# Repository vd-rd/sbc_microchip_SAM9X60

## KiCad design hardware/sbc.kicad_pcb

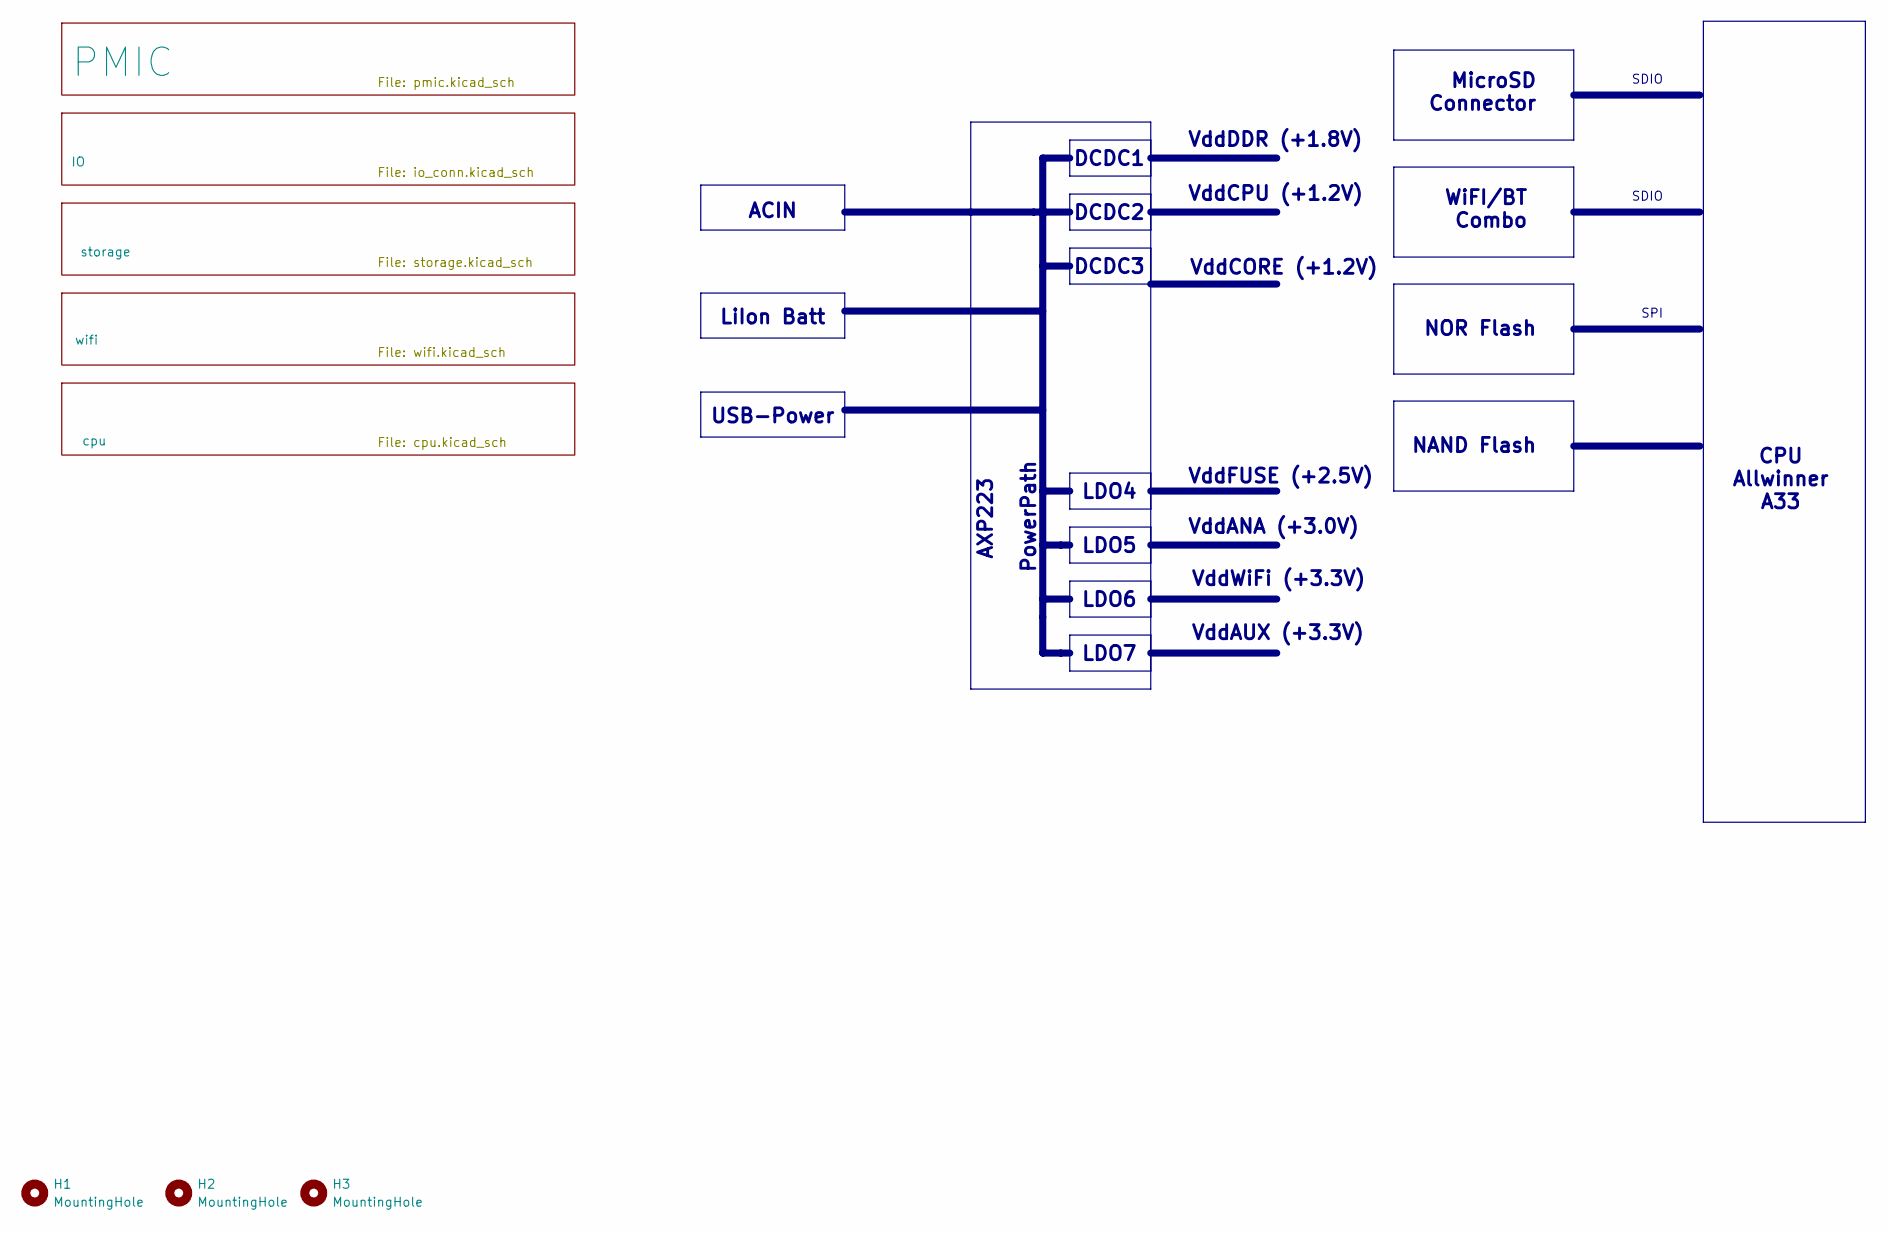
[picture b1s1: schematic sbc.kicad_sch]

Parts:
H1, H2, H3: MountingHole; MountingHole_2.7mm_M2.5

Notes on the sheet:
VddANA (+3.0V)
NOR Flash
LiIon Batt
WiFI/BT Combo
LDO7
LDO6
VddCORE (+1.2V)
DCDC1
PowerPath
SPI
VddWiFi (+3.3V)
DCDC2
CPU Allwinner A33
VddCPU (+1.2V)
SDIO
VddFUSE (+2.5V)
DCDC3
USB-Power
MicroSD Connector
LDO5
VddAUX (+3.3V)
VddDDR (+1.8V)
AXP223
ACIN
NAND Flash
LDO4

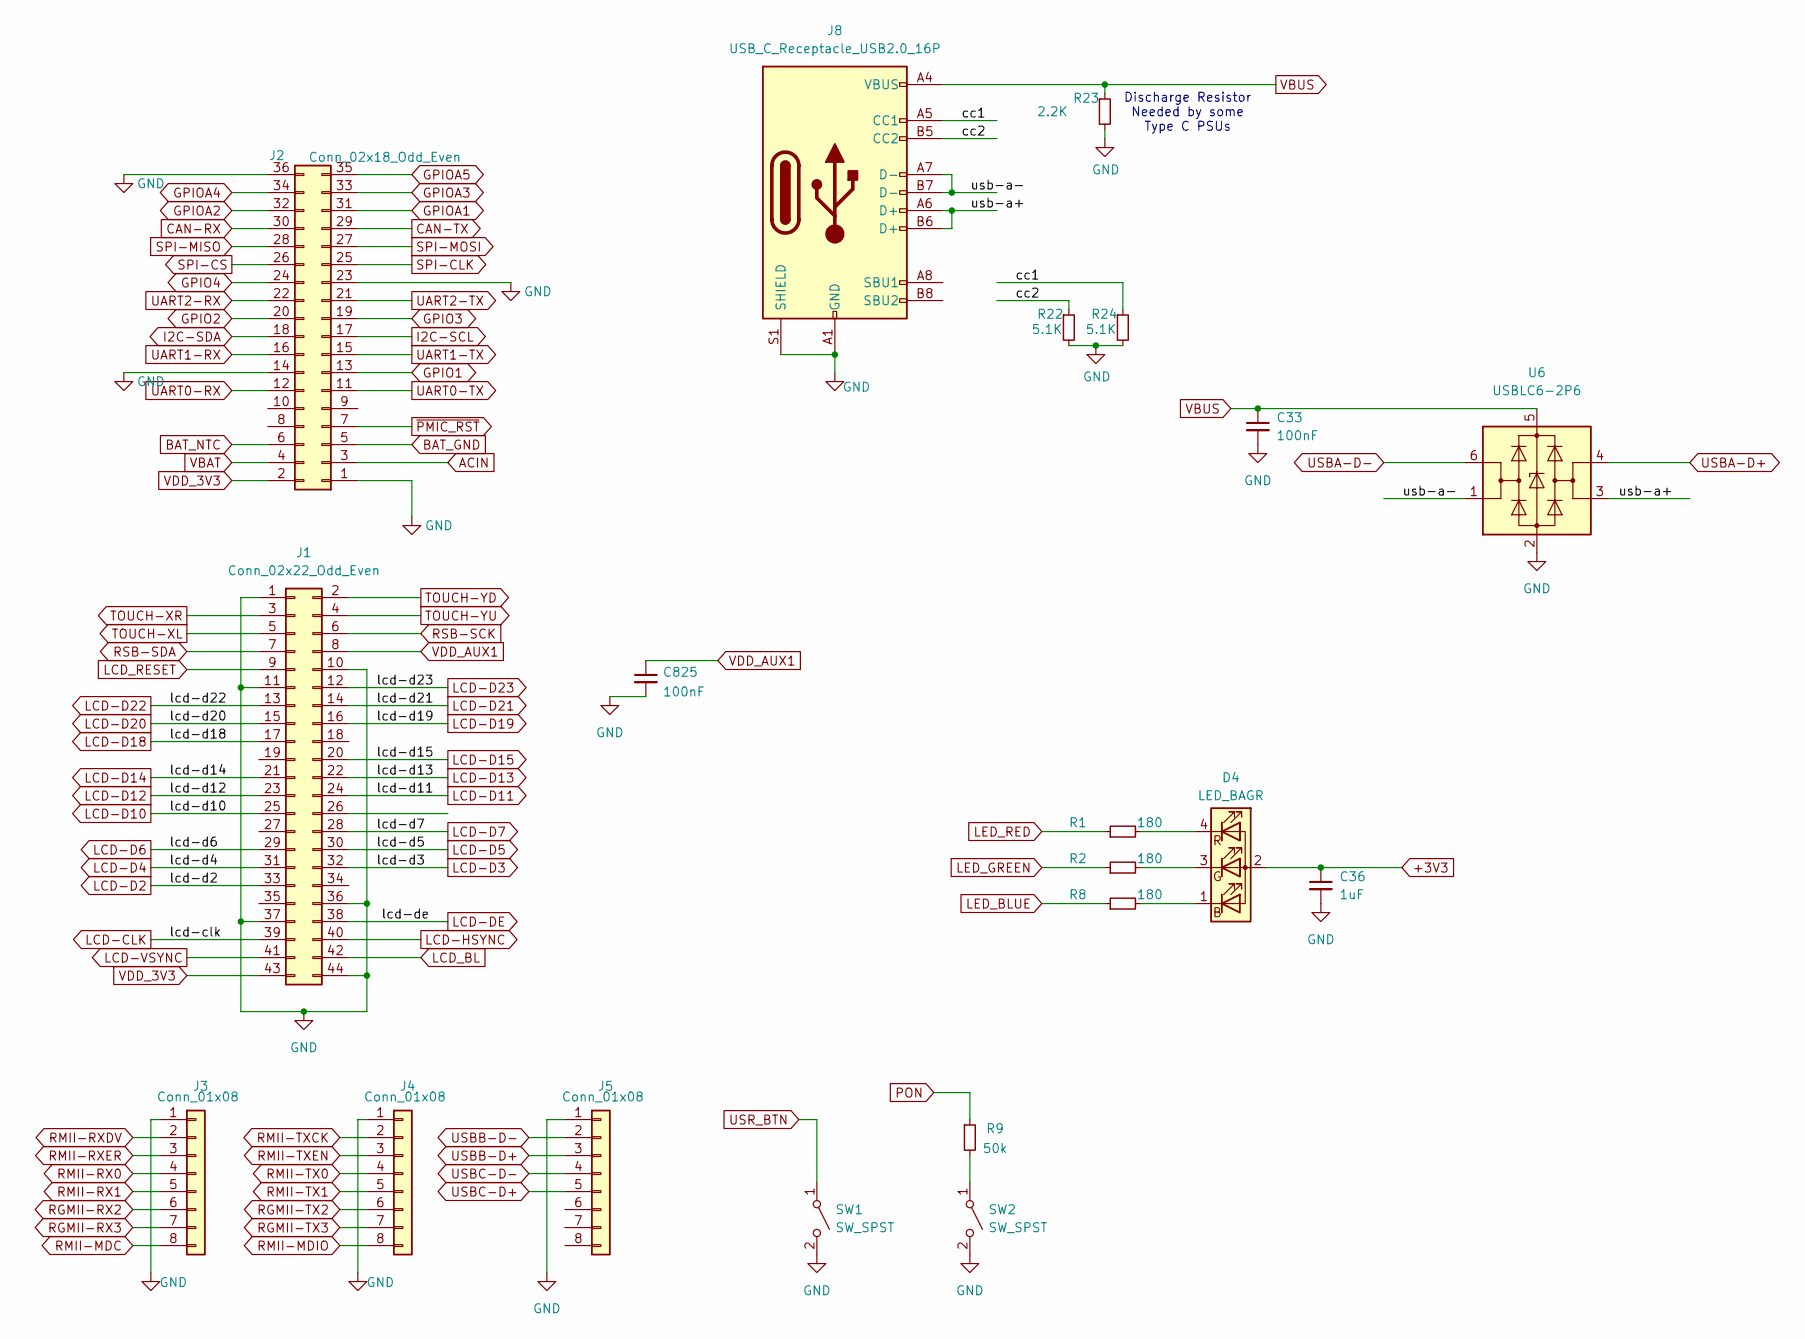
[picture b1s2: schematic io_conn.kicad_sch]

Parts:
C33, C825: 100nF; C_0402_1005Metric
C36: 1uF; C_0402_1005Metric
D4: LED_BAGR; LED_RGB_Optosupply_OSTB0805C1E-A-0.8T
J1: Conn_02x22_Odd_Even; PinHeader_2x22_P1.27mm_Vertical
J2: Conn_02x18_Odd_Even; PinHeader_2x18_P2.54mm_Vertical
J3, J4, J5: Conn_01x08; PinHeader_2x04_P1.27mm_Vertical
J8: USB_C_Receptacle_USB2.0_16P; USB_C_Receptacle_GCT_USB4105-xx-A_16P_TopMnt_Horizontal
R1, R2, R8: 180; R_0402_1005Metric
R9: 50k; R_0402_1005Metric
R22, R24: 5.1K; R_0402_1005Metric; Part Description Resistor 2.2K M1005 1% 63mW
R23: 2.2K; R_0402_1005Metric; Part Description Resistor 2.2K M1005 1% 63mW
SW1, SW2: SW_SPST; SW_SPST_EVQP7C
U6: USBLC6-2P6; SOT-23-6

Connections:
+3V3: C36.1, D4.2 (A)
/IO/cc1: J8.A5 (CC1), R24.1
/IO/cc2: J8.B5 (CC2), R22.1
/IO/usb-a+: J8.A6 (D+), J8.B6 (D+), U6.3 (I/O2)
/IO/usb-a-: J8.A7 (D-), J8.B7 (D-), U6.1 (I/O1)
ACIN: J2.3; also elsewhere on the board
BAT_GND: J2.5
BAT_NTC: J2.6; also elsewhere on the board
CAN-RX: J2.30; also elsewhere on the board
CAN-TX: J2.29; also elsewhere on the board
GPIO1: J2.13; also elsewhere on the board
GPIO2: J2.20; also elsewhere on the board
GPIO3: J2.19; also elsewhere on the board
GPIO4: J2.24; also elsewhere on the board
GPIOA1: J2.31; also elsewhere on the board
GPIOA2: J2.32; also elsewhere on the board
GPIOA3: J2.33; also elsewhere on the board
GPIOA4: J2.34; also elsewhere on the board
GPIOA5: J2.35
I2C-SCL: J2.17; also elsewhere on the board
I2C-SDA: J2.18; also elsewhere on the board
LCD-CLK: J1.39; also elsewhere on the board
LCD-D2: J1.33; also elsewhere on the board
LCD-D3: J1.32; also elsewhere on the board
LCD-D4: J1.31; also elsewhere on the board
LCD-D5: J1.30; also elsewhere on the board
LCD-D6: J1.29; also elsewhere on the board
LCD-D7: J1.28; also elsewhere on the board
LCD-D10: J1.25; also elsewhere on the board
LCD-D11: J1.24; also elsewhere on the board
LCD-D12: J1.23; also elsewhere on the board
LCD-D13: J1.22; also elsewhere on the board
LCD-D14: J1.21; also elsewhere on the board
LCD-D15: J1.20; also elsewhere on the board
LCD-D18: J1.17; also elsewhere on the board
LCD-D19: J1.16; also elsewhere on the board
LCD-D20: J1.15; also elsewhere on the board
LCD-D21: J1.14; also elsewhere on the board
LCD-D22: J1.13; also elsewhere on the board
LCD-D23: J1.12; also elsewhere on the board
LCD-DE: J1.38; also elsewhere on the board
LCD-HSYNC: J1.40; also elsewhere on the board
LCD-VSYNC: J1.41; also elsewhere on the board
LCD_BL: J1.42; also elsewhere on the board
LCD_RESET: J1.9
LED_BLUE: R8.1; also elsewhere on the board
LED_GREEN: R2.1; also elsewhere on the board
LED_RED: R1.1; also elsewhere on the board
unnamed: D4.1 (BK), R8.2
unnamed: D4.3 (GK), R2.2
unnamed: D4.4 (RK), R1.2
unnamed: R9.2, SW2.1 (A)
PON: R9.1; also elsewhere on the board
RGMII-RX2: J3.6
RGMII-RX3: J3.7
RGMII-TX2: J4.6
RGMII-TX3: J4.7
RMII-MDC: J3.8; also elsewhere on the board
RMII-MDIO: J4.8; also elsewhere on the board
RMII-RX0: J3.4; also elsewhere on the board
RMII-RX1: J3.5; also elsewhere on the board
RMII-RXDV: J3.2; also elsewhere on the board
RMII-RXER: J3.3; also elsewhere on the board
RMII-TX0: J4.4; also elsewhere on the board
RMII-TX1: J4.5; also elsewhere on the board
RMII-TXCK: J4.2; also elsewhere on the board
RMII-TXEN: J4.3; also elsewhere on the board
RSB-SCK: J1.6
RSB-SDA: J1.7
SPI-CLK: J2.25; also elsewhere on the board
SPI-CS: J2.26; also elsewhere on the board
SPI-MISO: J2.28; also elsewhere on the board
SPI-MOSI: J2.27; also elsewhere on the board
TOUCH-XL: J1.5
TOUCH-XR: J1.3
TOUCH-YD: J1.2
TOUCH-YU: J1.4
UART0-RX: J2.12; also elsewhere on the board
UART0-TX: J2.11; also elsewhere on the board
UART1-RX: J2.16; also elsewhere on the board
UART1-TX: J2.15; also elsewhere on the board
UART2-RX: J2.22; also elsewhere on the board
UART2-TX: J2.21; also elsewhere on the board
USBA-D+: U6.4 (I/O2); also elsewhere on the board
USBA-D-: U6.6 (I/O1); also elsewhere on the board
USBB-D+: J5.3; also elsewhere on the board
USBB-D-: J5.2; also elsewhere on the board
USBC-D+: J5.5; also elsewhere on the board
USBC-D-: J5.4; also elsewhere on the board
USR_BTN: SW1.1 (A); also elsewhere on the board
VBAT: J2.4; also elsewhere on the board
VBUS: C33.1, J8.A4 (VBUS), J8.A9 (VBUS), J8.B4 (VBUS), J8.B9 (VBUS), R23.1, U6.5 (VBUS); also elsewhere on the board
VDD_3V3: J1.43, J2.2; also elsewhere on the board
VDD_AUX1: C825.1, J1.8; also elsewhere on the board
~PMIC_RST: J2.7; also elsewhere on the board

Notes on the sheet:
Discharge Resistor Needed by some Type C PSUs

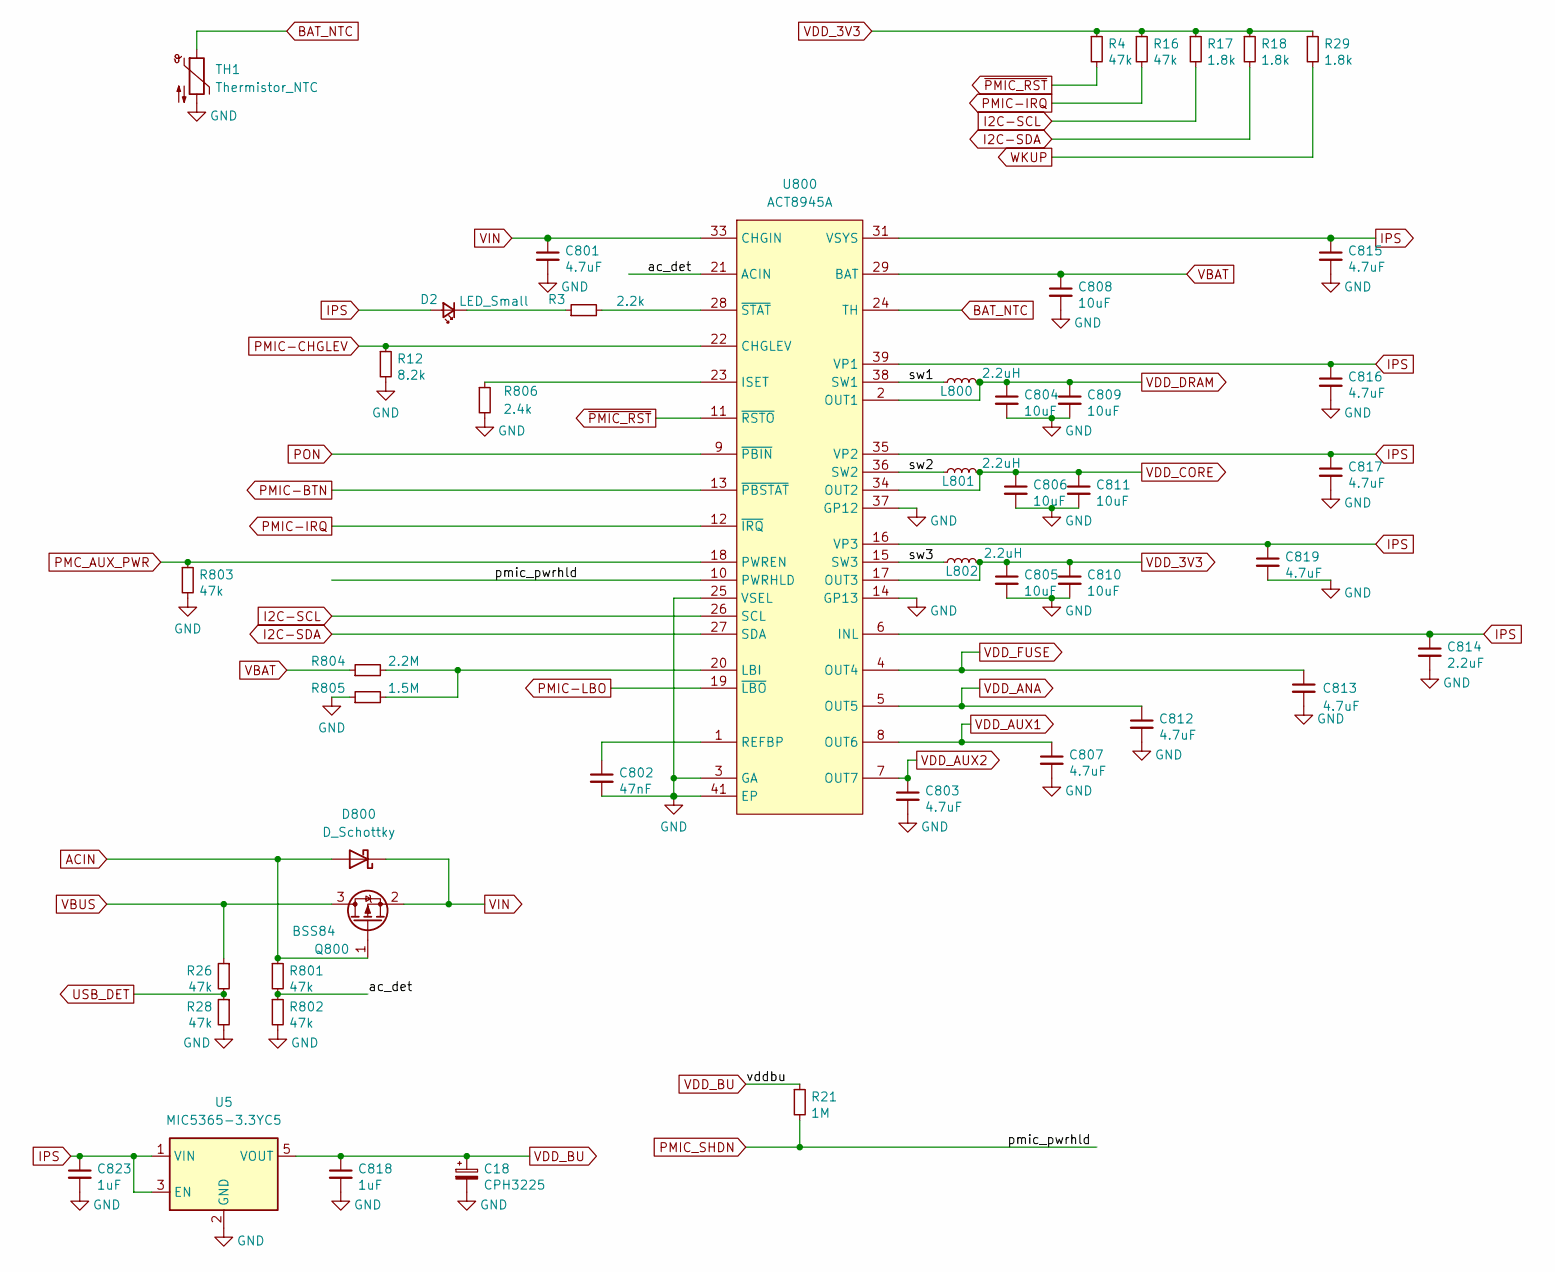
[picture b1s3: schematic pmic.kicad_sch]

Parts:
C18: CPH3225; C_1210_3225Metric
C801, C803, C807, C812, C813, C815, C816, C817, C819: 4.7uF; C_0603_1608Metric
C802: 47nF; C_0402_1005Metric
C804, C805, C806, C808, C809, C810, C811: 10uF; C_0603_1608Metric
C814: 2.2uF; C_0603_1608Metric
C818, C823: 1uF; C_0402_1005Metric
D2: LED_Small; LED_0603_1608Metric
D800: D_Schottky; D_SOD-523
L800, L801, L802: 2.2uH; L_Wuerth_MAPI-2510
Q800: BSS84; SOT-323_SC-70
R3: 2.2k; R_0402_1005Metric
R4, R16, R26, R28, R801, R802, R803: 47k; R_0402_1005Metric
R12: 8.2k; R_0402_1005Metric
R17, R18, R29: 1.8k; R_0402_1005Metric
R21: 1M; R_0402_1005Metric
R804: 2.2M; R_0402_1005Metric
R805: 1.5M; R_0402_1005Metric
R806: 2.4k; R_0402_1005Metric
TH1: Thermistor_NTC; R_0603_1608Metric
U5: MIC5365-3.3YC5; SOT-353_SC-70-5
U800: ACT8945A; TQFN-40-1EP_5x5mm_P0.4mm_EP3.5x3.5mm_ThermalVias

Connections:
/PMIC/ac_det: R801.2, R802.1, U800.21 (ACIN)
/PMIC/sw1: L800.1, U800.38 (SW1)
/PMIC/sw2: L801.1, U800.36 (SW2)
/PMIC/sw3: L802.1, U800.15 (SW3)
ACIN: D800.2 (A), Q800.1 (G), R801.1; also elsewhere on the board
BAT_NTC: TH1.1, U800.24 (TH); also elsewhere on the board
I2C-SCL: R17.2, U800.26 (SCL); also elsewhere on the board
I2C-SDA: R18.2, U800.27 (SDA); also elsewhere on the board
IPS: C814.1, C815.1, C816.1, C817.1, C819.1, C823.1, D2.2 (A), U5.1 (VIN), U5.3 (EN), U800.6 (INL), U800.16 (VP3), U800.31 (VSYS), U800.32 (VSYS), U800.35 (VP2), U800.39 (VP1)
unnamed: D2.1 (K), R3.1
unnamed: R806.1, U800.23 (ISET)
unnamed: R804.2, R805.2, U800.20 (LBI)
unnamed: C802.1, U800.1 (REFBP)
unnamed: R3.2, U800.28 (~STAT)
PMC_AUX_PWR: R803.1, U800.18 (PWREN); also elsewhere on the board
PMIC-BTN: U800.13 (~PBSTAT); also elsewhere on the board
PMIC-CHGLEV: R12.1, U800.22 (CHGLEV); also elsewhere on the board
PMIC-IRQ: R16.2, U800.12 (~IRQ); also elsewhere on the board
PMIC-LBO: U800.19 (~LBO); also elsewhere on the board
PMIC_SHDN: R21.2, U800.10 (PWRHLD); also elsewhere on the board
PON: U800.9 (~PBIN); also elsewhere on the board
USB_DET: R26.2, R28.1; also elsewhere on the board
VBAT: C808.1, R804.1, U800.29 (BAT), U800.30 (BAT); also elsewhere on the board
VBUS: Q800.3 (D), R26.1; also elsewhere on the board
VDD_3V3: C805.1, C810.1, L802.2, R4.1, R16.1, R17.1, R18.1, R29.1, U800.17 (OUT3); also elsewhere on the board
VDD_ANA: C812.1, U800.5 (OUT5); also elsewhere on the board
VDD_AUX1: C807.1, U800.8 (OUT6); also elsewhere on the board
VDD_AUX2: C803.1, U800.7 (OUT7); also elsewhere on the board
VDD_BU: C18.1, C818.1, R21.1, U5.5 (VOUT); also elsewhere on the board
VDD_CORE: C806.1, C811.1, L801.2, U800.34 (OUT2); also elsewhere on the board
VDD_DRAM: C804.1, C809.1, L800.2, U800.2 (OUT1); also elsewhere on the board
VDD_FUSE: C813.1, U800.4 (OUT4)
VIN: C801.1, D800.1 (K), Q800.2 (S), U800.33 (CHGIN)
WKUP: R29.2; also elsewhere on the board
~PMIC_RST: R4.2, U800.11 (~RSTO); also elsewhere on the board

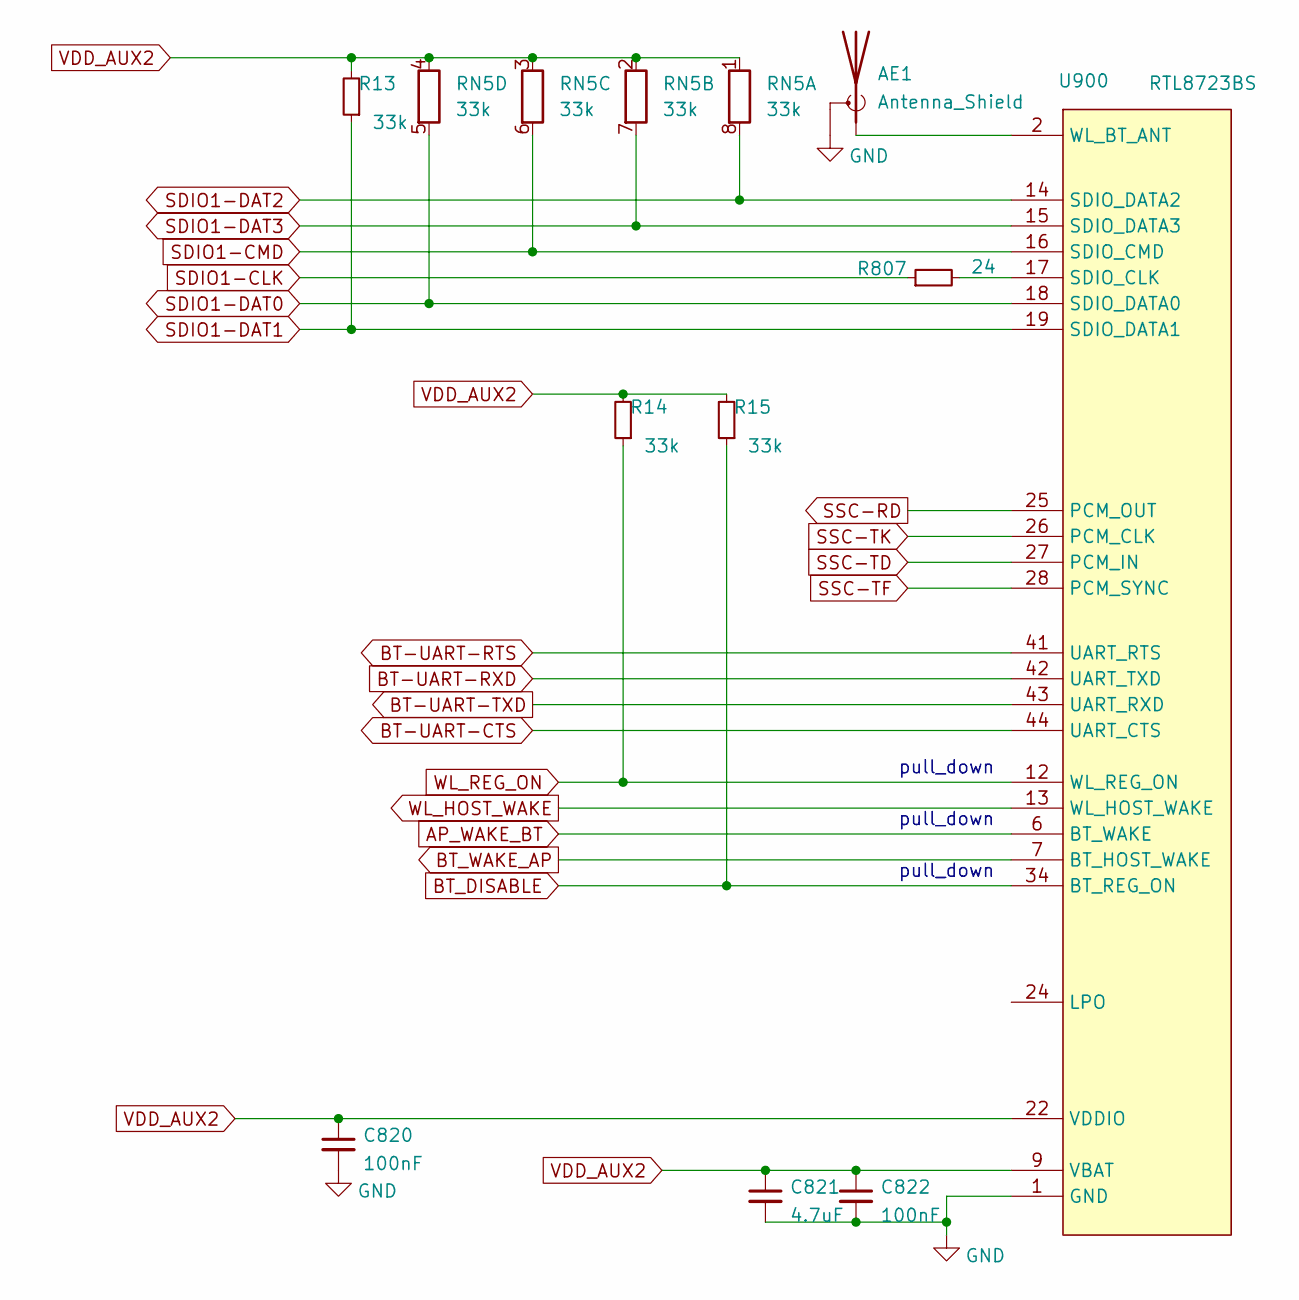
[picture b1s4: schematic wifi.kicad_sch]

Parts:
AE1: Antenna_Shield; U.FL_Hirose_U.FL-R-SMT-1_Vertical
C820, C822: 100nF; C_0402_1005Metric
C821: 4.7uF; C_0603_1608Metric
R13, R14, R15: 33k; R_0402_1005Metric
R807: 24; R_0402_1005Metric
RN5: 33k; R_Array_Concave_4x0402
U900: RTL8723BS; lga44_12x12mm_P0.9

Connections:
AP_WAKE_BT: U900.6 (BT_WAKE); also elsewhere on the board
BT-UART-CTS: U900.44 (UART_CTS); also elsewhere on the board
BT-UART-RXD: U900.42 (UART_TXD); also elsewhere on the board
BT-UART-TXD: U900.43 (UART_RXD); also elsewhere on the board
BT_DISABLE: R15.1, U900.34 (BT_REG_ON); also elsewhere on the board
BT_WAKE_AP: U900.7 (BT_HOST_WAKE); also elsewhere on the board
unnamed: AE1.1 (A), U900.2 (WL_BT_ANT)
unnamed: R807.2, U900.17 (SDIO_CLK)
SDIO1-CLK: R807.1; also elsewhere on the board
SDIO1-CMD: RN5.6 (R3.2), U900.16 (SDIO_CMD); also elsewhere on the board
SDIO1-DAT0: RN5.5 (R4.2), U900.18 (SDIO_DATA0); also elsewhere on the board
SDIO1-DAT1: R13.1, U900.19 (SDIO_DATA1); also elsewhere on the board
SDIO1-DAT2: RN5.8 (R1.2), U900.14 (SDIO_DATA2); also elsewhere on the board
SDIO1-DAT3: RN5.7 (R2.2), U900.15 (SDIO_DATA3); also elsewhere on the board
SSC-RD: U900.25 (PCM_OUT); also elsewhere on the board
SSC-TD: U900.27 (PCM_IN); also elsewhere on the board
SSC-TF: U900.28 (PCM_SYNC); also elsewhere on the board
SSC-TK: U900.26 (PCM_CLK); also elsewhere on the board
VDD_AUX2: C820.1, C821.1, C822.1, R13.2, R14.2, R15.2, RN5.1 (R1.1), RN5.2 (R2.1), RN5.3 (R3.1), RN5.4 (R4.1), U900.9 (VBAT), U900.22 (VDDIO); also elsewhere on the board
WL_HOST_WAKE: U900.13 (WL_HOST_WAKE); also elsewhere on the board
WL_REG_ON: R14.1, U900.12 (WL_REG_ON); also elsewhere on the board

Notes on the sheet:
pull_down

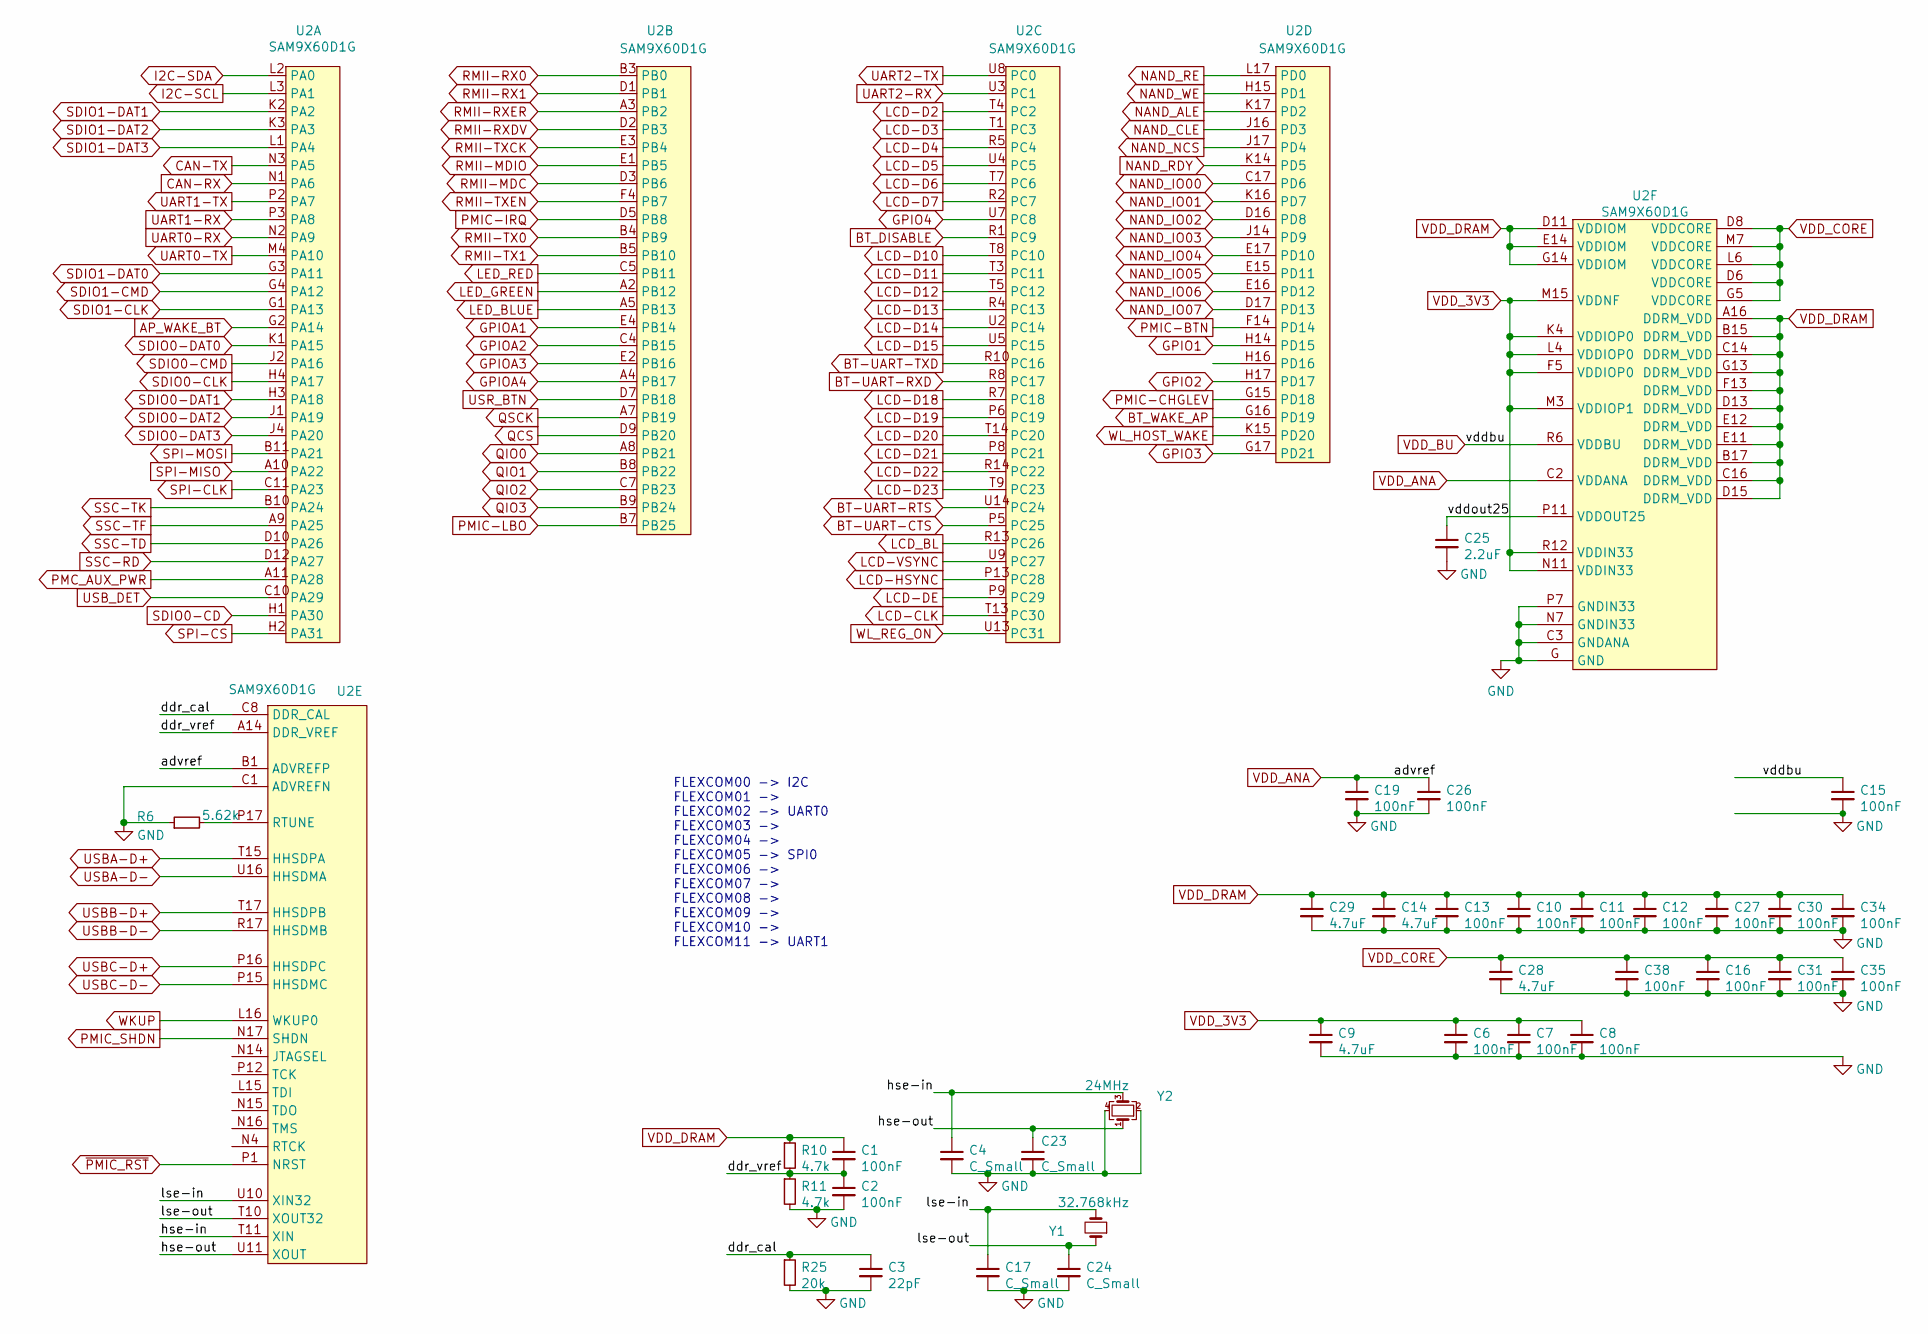
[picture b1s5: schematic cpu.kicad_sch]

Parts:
C1, C2, C6, C7, C8, C10, C11, C12, C13, C15, C16, C19, C26, C27, C30, C31, C34, C35, C38: 100nF; C_0402_1005Metric
C3: 22pF; C_0402_1005Metric
C4, C17, C23, C24: C_Small; C_0402_1005Metric
C9, C14, C28, C29: 4.7uF; C_0603_1608Metric
C25: 2.2uF; C_0402_1005Metric
R6: 5.62k; R_0402_1005Metric
R10, R11: 4.7k; R_0402_1005Metric
R25: 20k; R_0402_1005Metric
U2: SAM9X60D1G
Y1: 32.768kHz; Crystal_SMD_3215-2Pin_3.2x1.5mm
Y2: 24MHz; Crystal_SMD_3225-4Pin_3.2x2.5mm

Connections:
/cpu/ddr_cal: C3.1, R25.1, U2.C8 (DDR_CAL)
/cpu/ddr_vref: C1.2, C2.1, R10.2, R11.1, U2.A14 (DDR_VREF)
/cpu/hse-in: C4.1, U2.T11 (XIN), Y2.3
/cpu/hse-out: C23.1, U2.U11 (XOUT), Y2.1
/cpu/lse-in: C17.1, U2.U10 (XIN32), Y1.2
/cpu/lse-out: C24.1, U2.T10 (XOUT32), Y1.1
/cpu/vddout25: C25.1, U2.P11 (VDDOUT25)
AP_WAKE_BT: U2.G2 (PA14); also elsewhere on the board
BT-UART-CTS: U2.P5 (PC25); also elsewhere on the board
BT-UART-RXD: U2.R8 (PC17); also elsewhere on the board
BT-UART-TXD: U2.R10 (PC16); also elsewhere on the board
BT_DISABLE: U2.R1 (PC9); also elsewhere on the board
BT_WAKE_AP: U2.G16 (PD19); also elsewhere on the board
CAN-RX: U2.N1 (PA6); also elsewhere on the board
CAN-TX: U2.N3 (PA5); also elsewhere on the board
GPIO1: U2.H14 (PD15); also elsewhere on the board
GPIO2: U2.H17 (PD17); also elsewhere on the board
GPIO3: U2.G17 (PD21); also elsewhere on the board
GPIO4: U2.U7 (PC8); also elsewhere on the board
GPIOA1: U2.E4 (PB14); also elsewhere on the board
GPIOA2: U2.C4 (PB15); also elsewhere on the board
GPIOA3: U2.E2 (PB16); also elsewhere on the board
GPIOA4: U2.A4 (PB17); also elsewhere on the board
I2C-SCL: U2.L3 (PA1); also elsewhere on the board
I2C-SDA: U2.L2 (PA0); also elsewhere on the board
LCD-CLK: U2.T13 (PC30); also elsewhere on the board
LCD-D2: U2.T4 (PC2); also elsewhere on the board
LCD-D3: U2.T1 (PC3); also elsewhere on the board
LCD-D4: U2.R5 (PC4); also elsewhere on the board
LCD-D5: U2.U4 (PC5); also elsewhere on the board
LCD-D6: U2.T7 (PC6); also elsewhere on the board
LCD-D7: U2.R2 (PC7); also elsewhere on the board
LCD-D10: U2.T8 (PC10); also elsewhere on the board
LCD-D11: U2.T3 (PC11); also elsewhere on the board
LCD-D12: U2.T5 (PC12); also elsewhere on the board
LCD-D13: U2.R4 (PC13); also elsewhere on the board
LCD-D14: U2.U2 (PC14); also elsewhere on the board
LCD-D15: U2.U5 (PC15); also elsewhere on the board
LCD-D18: U2.R7 (PC18); also elsewhere on the board
LCD-D19: U2.P6 (PC19); also elsewhere on the board
LCD-D20: U2.T14 (PC20); also elsewhere on the board
LCD-D21: U2.P8 (PC21); also elsewhere on the board
LCD-D22: U2.R14 (PC22); also elsewhere on the board
LCD-D23: U2.T9 (PC23); also elsewhere on the board
LCD-DE: U2.P9 (PC29); also elsewhere on the board
LCD-HSYNC: U2.P13 (PC28); also elsewhere on the board
LCD-VSYNC: U2.U9 (PC27); also elsewhere on the board
LCD_BL: U2.R13 (PC26); also elsewhere on the board
LED_BLUE: U2.A5 (PB13); also elsewhere on the board
LED_GREEN: U2.A2 (PB12); also elsewhere on the board
LED_RED: U2.C5 (PB11); also elsewhere on the board
NAND_ALE: U2.K17 (PD2); also elsewhere on the board
NAND_CLE: U2.J16 (PD3); also elsewhere on the board
NAND_IO00: U2.C17 (PD6); also elsewhere on the board
NAND_IO01: U2.K16 (PD7); also elsewhere on the board
NAND_IO02: U2.D16 (PD8); also elsewhere on the board
NAND_IO03: U2.J14 (PD9); also elsewhere on the board
NAND_IO04: U2.E17 (PD10); also elsewhere on the board
NAND_IO05: U2.E15 (PD11); also elsewhere on the board
NAND_IO06: U2.E16 (PD12); also elsewhere on the board
NAND_IO07: U2.D17 (PD13); also elsewhere on the board
NAND_NCS: U2.J17 (PD4); also elsewhere on the board
NAND_RDY: U2.K14 (PD5); also elsewhere on the board
NAND_RE: U2.L17 (PD0); also elsewhere on the board
NAND_WE: U2.H15 (PD1); also elsewhere on the board
unnamed: R6.2, U2.P17 (RTUNE)
PMC_AUX_PWR: U2.A11 (PA28); also elsewhere on the board
PMIC-BTN: U2.F14 (PD14); also elsewhere on the board
PMIC-CHGLEV: U2.G15 (PD18); also elsewhere on the board
PMIC-IRQ: U2.D5 (PB8); also elsewhere on the board
PMIC-LBO: U2.B7 (PB25); also elsewhere on the board
PMIC_SHDN: U2.N17 (SHDN); also elsewhere on the board
QCS: U2.D9 (PB20); also elsewhere on the board
QIO0: U2.A8 (PB21); also elsewhere on the board
QIO1: U2.B8 (PB22); also elsewhere on the board
QIO2: U2.C7 (PB23); also elsewhere on the board
QIO3: U2.B9 (PB24); also elsewhere on the board
QSCK: U2.A7 (PB19); also elsewhere on the board
RMII-MDC: U2.D3 (PB6); also elsewhere on the board
RMII-MDIO: U2.E1 (PB5); also elsewhere on the board
RMII-RX0: U2.B3 (PB0); also elsewhere on the board
RMII-RX1: U2.D1 (PB1); also elsewhere on the board
RMII-RXDV: U2.D2 (PB3); also elsewhere on the board
RMII-RXER: U2.A3 (PB2); also elsewhere on the board
RMII-TX0: U2.B4 (PB9); also elsewhere on the board
RMII-TX1: U2.B5 (PB10); also elsewhere on the board
RMII-TXCK: U2.E3 (PB4); also elsewhere on the board
RMII-TXEN: U2.F4 (PB7); also elsewhere on the board
SDIO0-CD: U2.H1 (PA30); also elsewhere on the board
SDIO0-CLK: U2.H4 (PA17); also elsewhere on the board
SDIO0-CMD: U2.J2 (PA16); also elsewhere on the board
SDIO0-DAT0: U2.K1 (PA15); also elsewhere on the board
SDIO0-DAT1: U2.H3 (PA18); also elsewhere on the board
SDIO0-DAT2: U2.J1 (PA19); also elsewhere on the board
SDIO0-DAT3: U2.J4 (PA20); also elsewhere on the board
SDIO1-CLK: U2.G1 (PA13); also elsewhere on the board
SDIO1-CMD: U2.G4 (PA12); also elsewhere on the board
SDIO1-DAT0: U2.G3 (PA11); also elsewhere on the board
SDIO1-DAT1: U2.K2 (PA2); also elsewhere on the board
SDIO1-DAT2: U2.K3 (PA3); also elsewhere on the board
SDIO1-DAT3: U2.L1 (PA4); also elsewhere on the board
SPI-CLK: U2.C11 (PA23); also elsewhere on the board
SPI-CS: U2.H2 (PA31); also elsewhere on the board
SPI-MISO: U2.A10 (PA22); also elsewhere on the board
SPI-MOSI: U2.B11 (PA21); also elsewhere on the board
SSC-RD: U2.D12 (PA27); also elsewhere on the board
SSC-TD: U2.D10 (PA26); also elsewhere on the board
SSC-TF: U2.A9 (PA25); also elsewhere on the board
SSC-TK: U2.B10 (PA24); also elsewhere on the board
UART0-RX: U2.N2 (PA9); also elsewhere on the board
UART0-TX: U2.M4 (PA10); also elsewhere on the board
UART1-RX: U2.P3 (PA8); also elsewhere on the board
UART1-TX: U2.P2 (PA7); also elsewhere on the board
UART2-RX: U2.U3 (PC1); also elsewhere on the board
UART2-TX: U2.U8 (PC0); also elsewhere on the board
USBA-D+: U2.T15 (HHSDPA); also elsewhere on the board
USBA-D-: U2.U16 (HHSDMA); also elsewhere on the board
USBB-D+: U2.T17 (HHSDPB); also elsewhere on the board
USBB-D-: U2.R17 (HHSDMB); also elsewhere on the board
USBC-D+: U2.P16 (HHSDPC); also elsewhere on the board
USBC-D-: U2.P15 (HHSDMC); also elsewhere on the board
USB_DET: U2.C10 (PA29); also elsewhere on the board
USR_BTN: U2.D7 (PB18); also elsewhere on the board
VDD_3V3: C6.1, C7.1, C8.1, C9.1, U2.F5 (VDDIOP0), U2.K4 (VDDIOP0), U2.L4 (VDDIOP0), U2.M3 (VDDIOP1), U2.M15 (VDDNF), U2.N11 (VDDIN33), U2.R12 (VDDIN33); also elsewhere on the board
VDD_ANA: C19.1, C26.1, U2.B1 (ADVREFP), U2.C2 (VDDANA); also elsewhere on the board
VDD_BU: C15.1, U2.R6 (VDDBU); also elsewhere on the board
VDD_CORE: C16.1, C28.1, C31.1, C35.1, C38.1, U2.D6 (VDDCORE), U2.D8 (VDDCORE), U2.G5 (VDDCORE), U2.L6 (VDDCORE), U2.M7 (VDDCORE); also elsewhere on the board
VDD_DRAM: C1.1, C10.1, C11.1, C12.1, C13.1, C14.1, C27.1, C29.1, C30.1, C34.1, R10.1, U2.A16 (DDRM_VDD), U2.B15 (DDRM_VDD), U2.B17 (DDRM_VDD), U2.C14 (DDRM_VDD), U2.C16 (DDRM_VDD), U2.D11 (VDDIOM), U2.D13 (DDRM_VDD), U2.D15 (DDRM_VDD), U2.E11 (DDRM_VDD), U2.E12 (DDRM_VDD), U2.E14 (VDDIOM), U2.F13 (DDRM_VDD), U2.G13 (DDRM_VDD), U2.G14 (VDDIOM); also elsewhere on the board
WKUP: U2.L16 (WKUP0); also elsewhere on the board
WL_HOST_WAKE: U2.K15 (PD20); also elsewhere on the board
WL_REG_ON: U2.U13 (PC31); also elsewhere on the board
~PMIC_RST: U2.P1 (NRST); also elsewhere on the board

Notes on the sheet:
FLEXCOM00 -> I2C FLEXCOM01 -> FLEXCOM02 -> UART0 FLEXCOM03 -> FLEXCOM04 -> FLEXCOM05 -> SPI0 FLEXCOM06 -> FLEXCOM07 -> FLEXCOM08 -> FLEXCOM09 -> FLEXCOM10 -> FLEXCOM11 -> UART1

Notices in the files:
sbc.kicad_pcb:
© VDRD
